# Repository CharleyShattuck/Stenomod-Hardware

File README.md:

# Stenomod-Hardware

TinyMod4 is the current keyboard. TinyModsplit is a prototype split version of TinyMod.

formerly:
In addition to the left hand module for stenomod15, the one with the split S- into two keys, we now have the three boards currently being used in stenomods. Stenomod16 is the new hinge model. Tiny-stenomod is the new TinyMod model.

KiCad footprints used here were found at https://github.com/ruiqimao/keyboard-pcb-guide

License for Gateron.pretty is not known as it was modified from the file "CHERRY\_PCB\_100H.kicad\_mod", obtained at  https://github.com/stormbard/Keyboard.pretty  which had no expressed license.

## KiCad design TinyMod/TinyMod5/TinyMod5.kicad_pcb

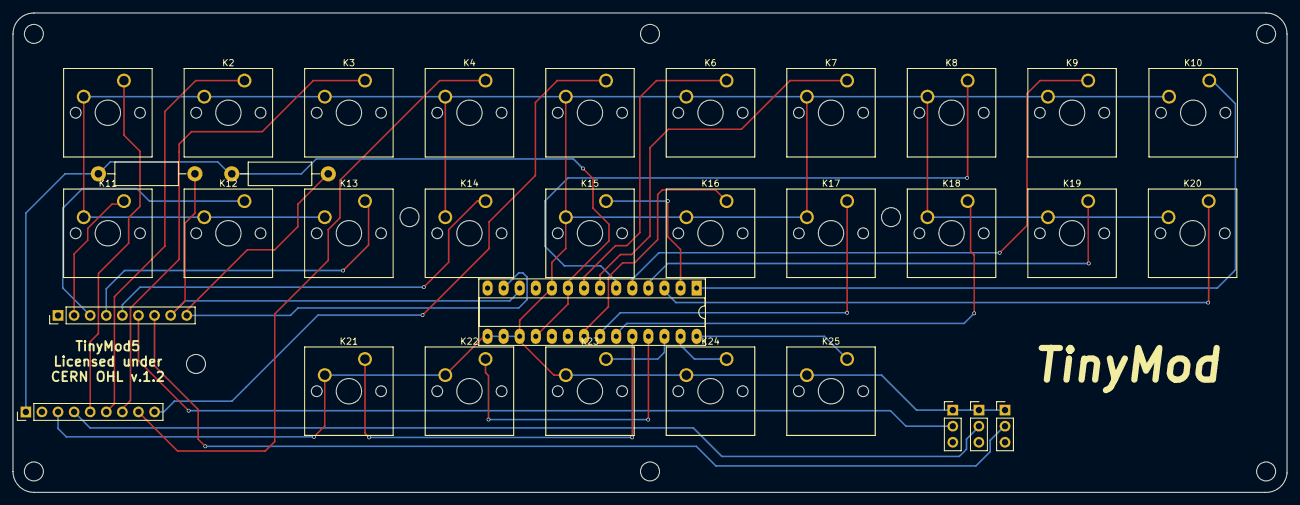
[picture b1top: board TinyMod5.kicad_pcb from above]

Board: 2 copper layers, 201.2 x 75.7 mm, 33 parts (0 on the bottom side), 32 nets.

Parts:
J1, J2: Conn_01x09; Pin_Header_Straight_1x09_Pitch2.54mm
J3: Slider Switch; Pin_Header_Straight_1x03_Pitch2.54mm
J4: Slider Switch 2; Pin_Header_Straight_1x03_Pitch2.54mm
J5: Slider Switch 3; Pin_Header_Straight_1x03_Pitch2.54mm
K1, K2, K3, K4, K5, K6, K7, K8, K9, K10, K11, K12, K13, K14, K15, K16, K17, K18, K19, K20, K21, K22, K23, K24, K25: KEYSW; SW_Cherry_MX1A_1.00u_PCB
R1, R2: R; R_Axial_DIN0411_L9.9mm_D3.6mm_P15.24mm_Horizontal
U1: MCP23017; DIP-28_W7.62mm_Socket_LongPads

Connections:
unnamed: J1.1, R1.1, R2.1, U1.9, U1.18
unnamed: J1.3, J3.1, J4.1, J5.1, K1.2, K2.2, K3.2, K4.2, K5.2, K6.2, K7.2, K8.2, K9.2, K10.2, K11.2, K12.2, K13.2, K14.2, K15.2, K16.2, K17.2, K18.2, K19.2, K20.2, K21.2, K22.2, K23.2, K24.2, K25.2, U1.10, U1.15, U1.16, U1.17
unnamed: J1.4, J4.2
unnamed: J1.5, K1.1
unnamed: J1.6, K2.1
unnamed: J1.7, K3.1
unnamed: J1.8, K4.1
unnamed: J1.9, K5.1
unnamed: J2.2, K11.1
unnamed: J2.3, K12.1
unnamed: J2.4, K13.1
unnamed: J2.5, K14.1
unnamed: J2.6, J3.2
unnamed: J2.7, J5.2
unnamed: J2.8, R1.2, U1.12
unnamed: J2.9, R2.2, U1.13
unnamed: K6.1, U1.8
unnamed: K7.1, U1.7
unnamed: K8.1, U1.6
unnamed: K9.1, U1.5
unnamed: K10.1, U1.1
unnamed: K15.1, U1.2
unnamed: K16.1, U1.21
unnamed: K17.1, U1.22
unnamed: K18.1, U1.23
unnamed: K19.1, U1.4
unnamed: K20.1, U1.3
unnamed: K21.1, U1.24
unnamed: K22.1, U1.25
unnamed: K23.1, U1.26
unnamed: K24.1, U1.27
unnamed: K25.1, U1.28

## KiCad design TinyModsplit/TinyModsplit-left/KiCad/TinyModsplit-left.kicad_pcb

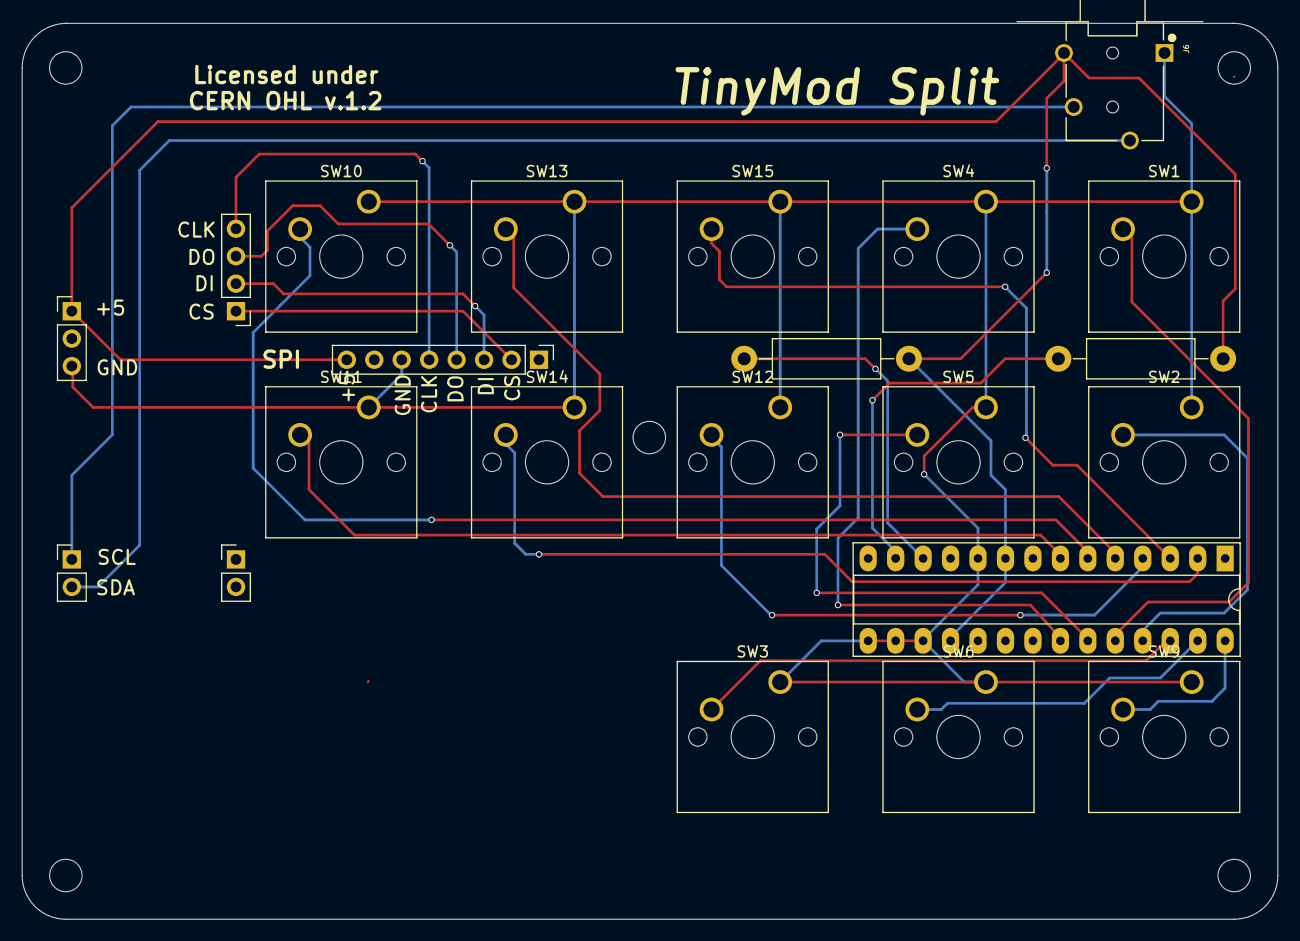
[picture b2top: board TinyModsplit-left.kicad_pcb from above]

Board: 2 copper layers, 116.2 x 83.0 mm, 22 parts (0 on the bottom side), 23 nets.

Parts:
J1: Conn_01x03; Pin_Header_Straight_1x03_Pitch2.54mm
J2, J5: Conn_01x02; Pin_Header_Straight_1x02_Pitch2.54mm
J3: Conn_01x08; Pin_Header_Straight_1x08_Pitch2.54mm
J6: SJ-43514; CUI_SJ-43514
J7: Conn_01x04; Pin_Header_Straight_1x04_Pitch2.54mm
R1, R2: R; R_Axial_DIN0411_L9.9mm_D3.6mm_P15.24mm_Horizontal
SW1, SW2, SW3, SW4, SW5, SW6, SW9, SW10, SW11, SW12, SW13, SW14, SW15: SW_DIP_x01; SW_Cherry_MX1A_1.00u_PCB
U1: MCP23017; DIP-28_W7.62mm_Socket_LongPads

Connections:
unnamed: J1.1, J3.8, J6.4, R1.1, R2.1, U1.9, U1.18
unnamed: J1.3, J3.6, J6.1, SW1.1, SW2.1, SW3.1, SW4.1, SW5.1, SW6.1, SW9.1, SW10.1, SW11.1, SW12.1, SW13.1, SW14.1, SW15.1, U1.10, U1.15, U1.16, U1.17
unnamed: J2.1, J6.2
unnamed: J2.2, J6.3
unnamed: J3.2, J7.1
unnamed: J3.3, J7.2
unnamed: J3.4, J7.3
unnamed: J3.5, J7.4
unnamed: R1.2, U1.12
unnamed: R2.2, U1.13
unnamed: SW1.2, U1.24
unnamed: SW2.2, U1.25
unnamed: SW3.2, U1.26
unnamed: SW4.2, U1.22
unnamed: SW5.2, U1.23
unnamed: SW6.2, U1.27
unnamed: SW9.2, U1.28
unnamed: SW10.2, U1.6
unnamed: SW11.2, U1.7
unnamed: SW12.2, U1.4
unnamed: SW13.2, U1.5
unnamed: SW14.2, U1.2
unnamed: SW15.2, U1.3

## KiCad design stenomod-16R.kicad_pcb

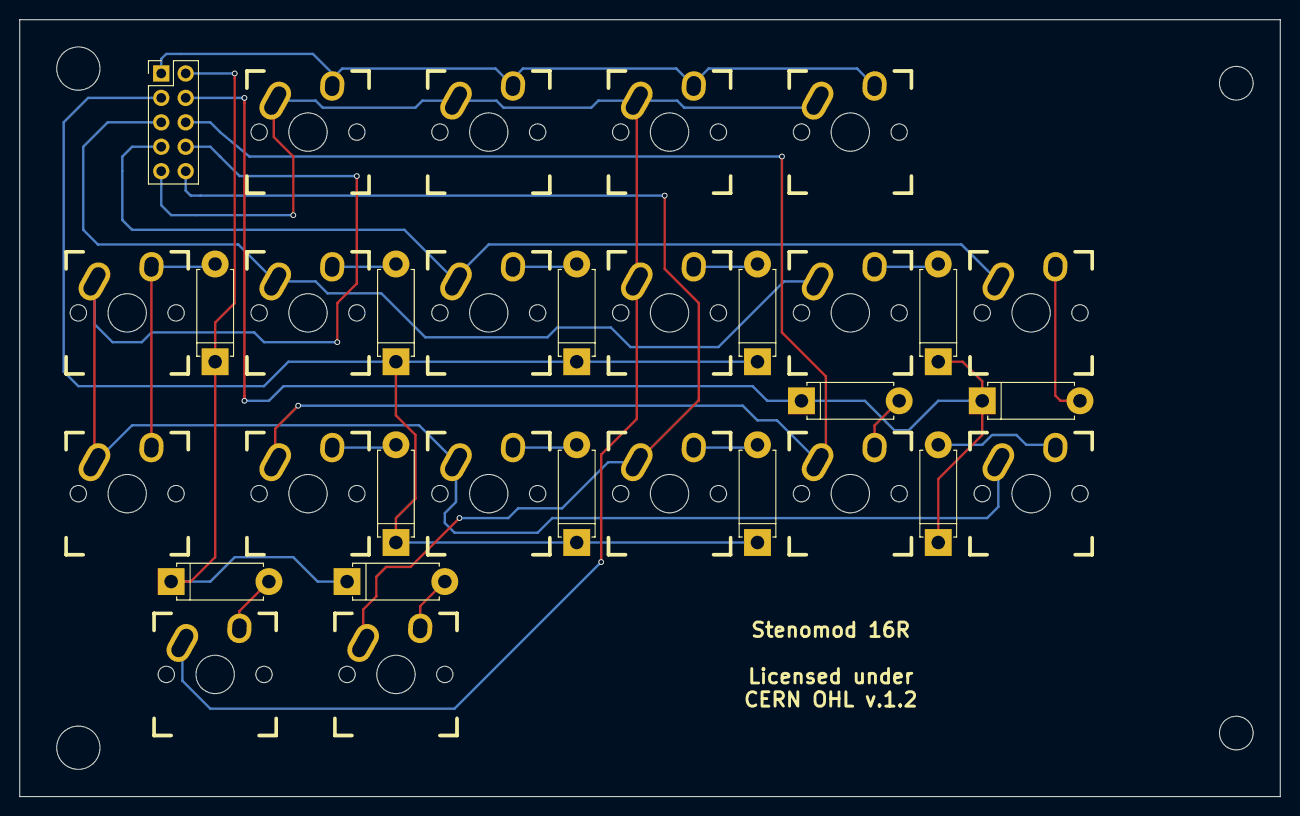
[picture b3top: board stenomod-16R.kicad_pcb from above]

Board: 2 copper layers, 131.1 x 80.8 mm, 32 parts (0 on the bottom side), 23 nets.

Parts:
D1, D2, D3, D4, D5, D6, D7, D8, D9, D10, D11, D12, D13: D; D_5W_P10.16mm_Horizontal
J_10: Conn_02x05_Odd_Even; Pin_Header_Straight_2x05_Pitch2.54mm
K1, K2, K3, K4, K5, K6, K7, K8, K9, K10, K11, K12, K13, K14, K15, K16, K17, K18: KEYSW; Mx_Alps_100

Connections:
unnamed: D1.1, D2.1, D6.1, D7.1, J_10.4
unnamed: D1.2, K1.2
unnamed: D2.2, K2.2
unnamed: D3.2, K3.2
unnamed: D4.2, K4.2
unnamed: D5.2, K5.2
unnamed: D6.2, K6.2
unnamed: D7.2, K7.2
unnamed: D8.2, K8.2
unnamed: D9.2, K9.2
unnamed: D3.1, D4.1, D5.1, D8.1, D9.1, D10.1, J_10.3
unnamed: D10.2, K10.2
unnamed: D11.1, D12.1, D13.1, J_10.2
unnamed: D11.2, K11.2, K14.2
unnamed: D12.2, K12.2
unnamed: D13.2, K13.2
unnamed: J_10.1, K15.2, K16.2, K17.2, K18.2
unnamed: J_10.5, K2.1, K5.1
unnamed: J_10.6, K7.1, K10.1
unnamed: J_10.7, K1.1, K4.1
unnamed: J_10.8, K6.1, K9.1, K11.1, K14.1
unnamed: J_10.9, K3.1, K13.1, K15.1, K16.1, K17.1, K18.1
unnamed: J_10.10, K8.1, K12.1

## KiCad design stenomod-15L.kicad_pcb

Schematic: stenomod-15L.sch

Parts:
D_#1234: D; D_DO-41_SOD81_P10.16mm_Horizontal
D_*12: D; D_DO-41_SOD81_P10.16mm_Horizontal
D_A1: D; D_DO-41_SOD81_P10.16mm_Horizontal
D_H1: D; D_DO-41_SOD81_P10.16mm_Horizontal
D_K1: D; D_DO-41_SOD81_P10.16mm_Horizontal
D_O1: D; D_DO-41_SOD81_P10.16mm_Horizontal
D_P1: D; D_DO-41_SOD81_P10.16mm_Horizontal
D_R1: D; D_DO-41_SOD81_P10.16mm_Horizontal
D_S1, D_S2: D; D_DO-41_SOD81_P10.16mm_Horizontal
D_T1: D; D_DO-41_SOD81_P10.16mm_Horizontal
D_W1: D; D_DO-41_SOD81_P10.16mm_Horizontal
P_0: CONN_02X05; IDC_Header_Straight_10pins
P_1, P_4: CONN_01X02; PINHEAD1-2
P_2, P_3: CONN_01X06; PINHEAD1-6
SW_#1, SW_#2, SW_#3, SW_#4: SW_PUSH; Gateron
SW_*1, SW_*2: SW_PUSH; Gateron
SW_A-1: SW_PUSH; Gateron
SW_H-1: SW_PUSH; Gateron
SW_K-1: SW_PUSH; Gateron
SW_O-1: SW_PUSH; Gateron
SW_P-1: SW_PUSH; Gateron
SW_R-1: SW_PUSH; Gateron
SW_S1, SW_S2: SW_PUSH; Gateron
SW_T-1: SW_PUSH; Gateron
SW_W-1: SW_PUSH; Gateron

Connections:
unnamed: D_#1234.1 (K), D_S1.1 (K), P_0.4, P_3.6
unnamed: D_#1234.2 (A), P_0.1, SW_#1.2, SW_#2.2, SW_#3.2, SW_#4.2
unnamed: D_*12.1 (K), D_A1.1 (K), D_O1.1 (K), D_R1.1 (K), P_0.2, P_3.4
unnamed: D_*12.2 (A), SW_*1.2, SW_*2.2
unnamed: D_A1.2 (A), SW_A-1.2
unnamed: D_H1.1 (K), D_K1.1 (K), D_P1.1 (K), D_S2.1 (K), D_T1.1 (K), D_W1.1 (K), P_3.3
unnamed: D_H1.2 (A), SW_H-1.2
unnamed: D_K1.2 (A), SW_K-1.2
unnamed: D_O1.2 (A), SW_O-1.2
unnamed: D_P1.2 (A), SW_P-1.2
unnamed: D_R1.2 (A), SW_R-1.2
unnamed: D_S1.2 (A), SW_S1.2
unnamed: D_S2.2 (A), SW_S2.2
unnamed: D_T1.2 (A), SW_T-1.2
unnamed: D_W1.2 (A), SW_W-1.2
unnamed: P_0.3, P_3.5
unnamed: P_0.5, P_2.1, SW_R-1.1, SW_S2.1
unnamed: P_0.6, P_2.2, SW_A-1.1, SW_T-1.1
unnamed: P_0.7, P_2.3, SW_K-1.1, SW_O-1.1
unnamed: P_0.8, P_2.4, SW_*1.1, SW_*2.1, SW_P-1.1
unnamed: P_0.9, P_2.5, SW_#1.1, SW_#2.1, SW_#3.1, SW_#4.1, SW_W-1.1
unnamed: P_0.10, P_2.6, SW_H-1.1, SW_S1.1

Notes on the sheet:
Copyright Charles Shattuck 2017 This schematic describes Open Hardware and is licensed under the CERN OHL v. 1.2.
A0 A1 A2 A3 A4 A5
11 S2 T K P W H
10 R A O * E U
9 F R P B L G
8 T S D Z # S1
TX Bolt Protocol made easier via wiring
← column pin
row pin ↓
Stenomod15 Left hand module with split S
You may redistribute and modify this documentation under the terms of the CERN OHL v. 1.2. (http://ohwr.org/cernohl). This documentation is distributed WITHOUT ANY EXPRESS OR IMPLIED WARRANTY, INCLUDING OF MERCHANTABILITY, SATISFACTORY QUALITY AND FITNESS FOR A PARTICULAR PURPOSE. Please see the CE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

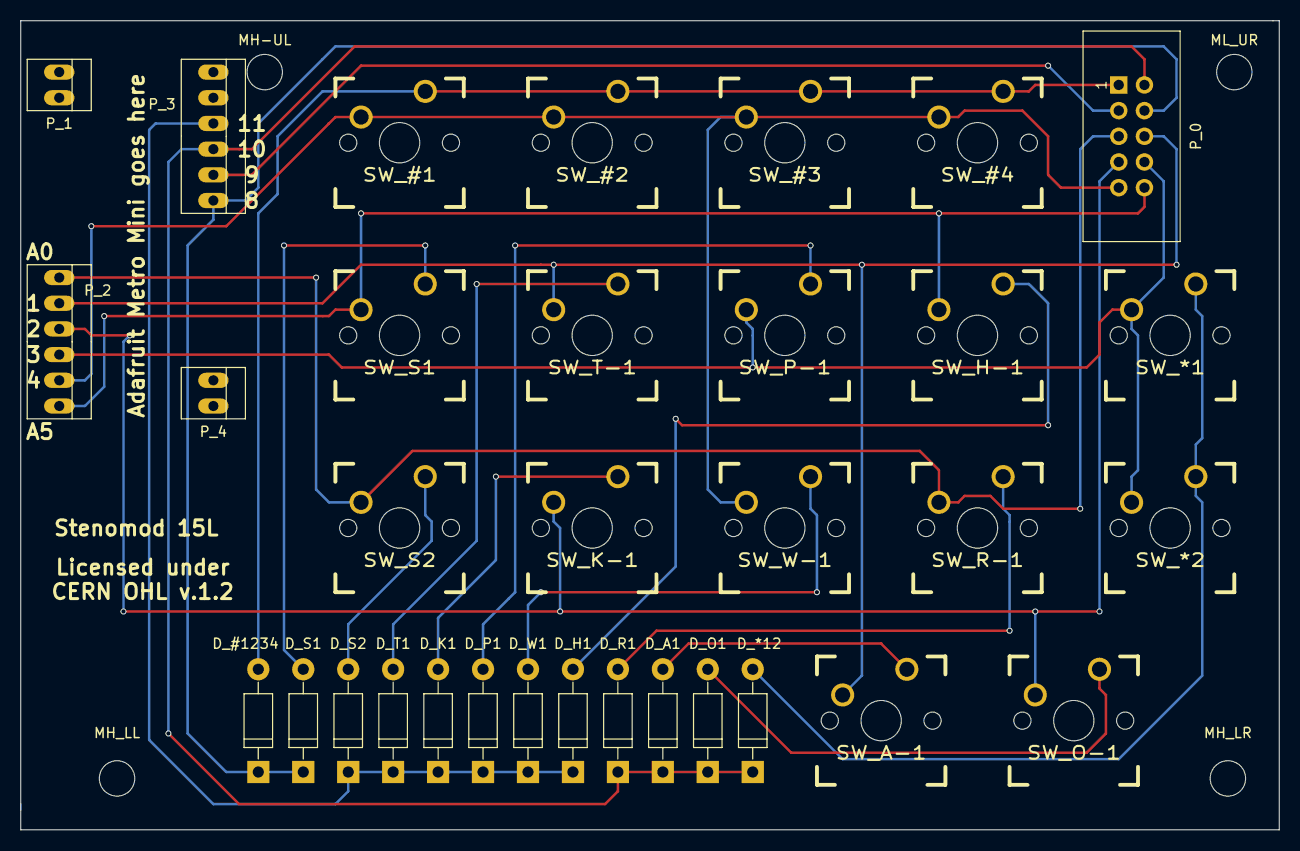
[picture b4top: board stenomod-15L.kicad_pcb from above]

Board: 2 copper layers, 124.5 x 80.0 mm, 37 parts (0 on the bottom side), 22 nets.

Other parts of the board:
MH-UL: MH_3.5mm; MountingHole_3.5mm
MH_LL: MH_3.5mm; MountingHole_3.5mm
MH_LR: MH_3.5mm; MountingHole_3.5mm
ML_UR: MH_3.5mm; MountingHole_3.5mm

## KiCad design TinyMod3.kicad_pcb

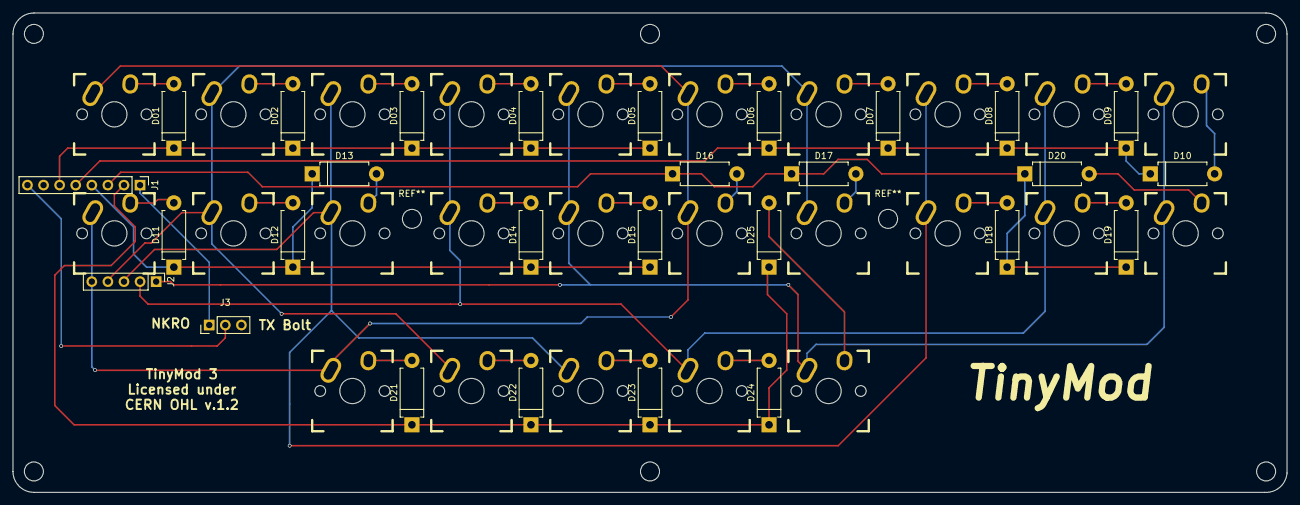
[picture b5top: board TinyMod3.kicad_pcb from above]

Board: 2 copper layers, 201.2 x 75.7 mm, 53 parts (0 on the bottom side), 37 nets.

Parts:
D01, D02, D03, D04, D05, D06, D07, D08, D09, D10, D11, D12, D13, D14, D15, D16, D17, D18, D19, D20, D21, D22, D23, D24, D25: D; D_DO-15_P10.16mm_Horizontal
J1: Conn_01x08; Pin_Header_Straight_1x08_Pitch2.54mm
J2: Conn_01x05; Pin_Header_Straight_1x05_Pitch2.54mm
J3: Slider Switch; Pin_Header_Straight_1x03_Pitch2.54mm
K01, K02, K03, K04, K05, K06, K07, K08, K09, K10, K11, K12, K13, K14, K15, K16, K17, K18, K19, K20, K21, K22, K23, K24, K25: KEYSW; Mx_Alps_100

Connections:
unnamed: D01.1, D02.1, D03.1, D04.1, D05.1, J1.6
unnamed: D01.2, K01.2
unnamed: D02.2, K02.2
unnamed: D03.2, K03.2
unnamed: D04.2, K04.2
unnamed: D05.2, K05.2
unnamed: D06.1, D07.1, D08.1, D09.1, D10.1, J1.5
unnamed: D06.2, K06.2
unnamed: D07.2, K07.2
unnamed: D08.2, K08.2
unnamed: D09.2, K09.2
unnamed: D10.2, K10.2
unnamed: D11.1, D12.1, D13.1, D14.1, D15.1, J1.4
unnamed: D11.2, K11.2
unnamed: D12.2, K12.2
unnamed: D13.2, K13.2
unnamed: D14.2, K14.2
unnamed: D15.2, K15.2
unnamed: D16.1, D17.1, D18.1, D19.1, D20.1, J1.3
unnamed: D16.2, K16.2
unnamed: D17.2, K17.2
unnamed: D18.2, K18.2
unnamed: D19.2, K19.2
unnamed: D20.2, K20.2
unnamed: D21.1, D22.1, D23.1, D24.1, D25.1, J1.2
unnamed: D21.2, K21.2
unnamed: D22.2, K22.2
unnamed: D23.2, K23.2
unnamed: D24.2, K24.2
unnamed: D25.2, K25.2
unnamed: J1.1, J3.1
unnamed: J1.8, J3.2
unnamed: J2.1, K05.1, K10.1, K15.1, K20.1, K25.1
unnamed: J2.2, K04.1, K09.1, K14.1, K19.1, K24.1
unnamed: J2.3, K03.1, K08.1, K13.1, K18.1, K23.1
unnamed: J2.4, K02.1, K07.1, K12.1, K17.1, K22.1
unnamed: J2.5, K01.1, K06.1, K11.1, K16.1, K21.1

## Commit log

2017-04-26 License added
2017-04-26 schematic and PCB
2017-04-26 Gateron footprint
2017-04-26 fix typo
2017-04-26 more info about Gateron.pretty
2017-04-26 another typo
2017-04-27 pdf and svg files added
2017-04-27 more text on the board
2018-05-22 stenomod Open Source hardware as of May 22, 2018
2018-05-22 Readme now mentions TinyMod and stenomod16
2018-05-22 README.md now mentions TinyMod and stenomod16 a
2018-07-25 Added 3D printed covers for the Arduinos
2019-02-06 TinyMod2
2019-02-27 Added TinyMod 3 cad files
2019-08-28 TinyMod4 PCB
2020-04-23 TinyMod4 schematic PDF
2021-03-11 TinyModsplit first prototype
2021-03-11 Mentioning TinyModsplit
2021-03-19 Fixed wiring errors, changed outline
2021-07-03 All the TinyMod4 Gerbers in one zip file.
    The way JLCPCB likes it.
2021-07-10 Sorted repo folders into keyboards and subfolders for KiCad and Gerber
2022-02-28 added cheat sheet
2022-06-05 TinyMod5 CAD files
    TinyMod5.zip is the Gerber files, as sent to JLCPCB
